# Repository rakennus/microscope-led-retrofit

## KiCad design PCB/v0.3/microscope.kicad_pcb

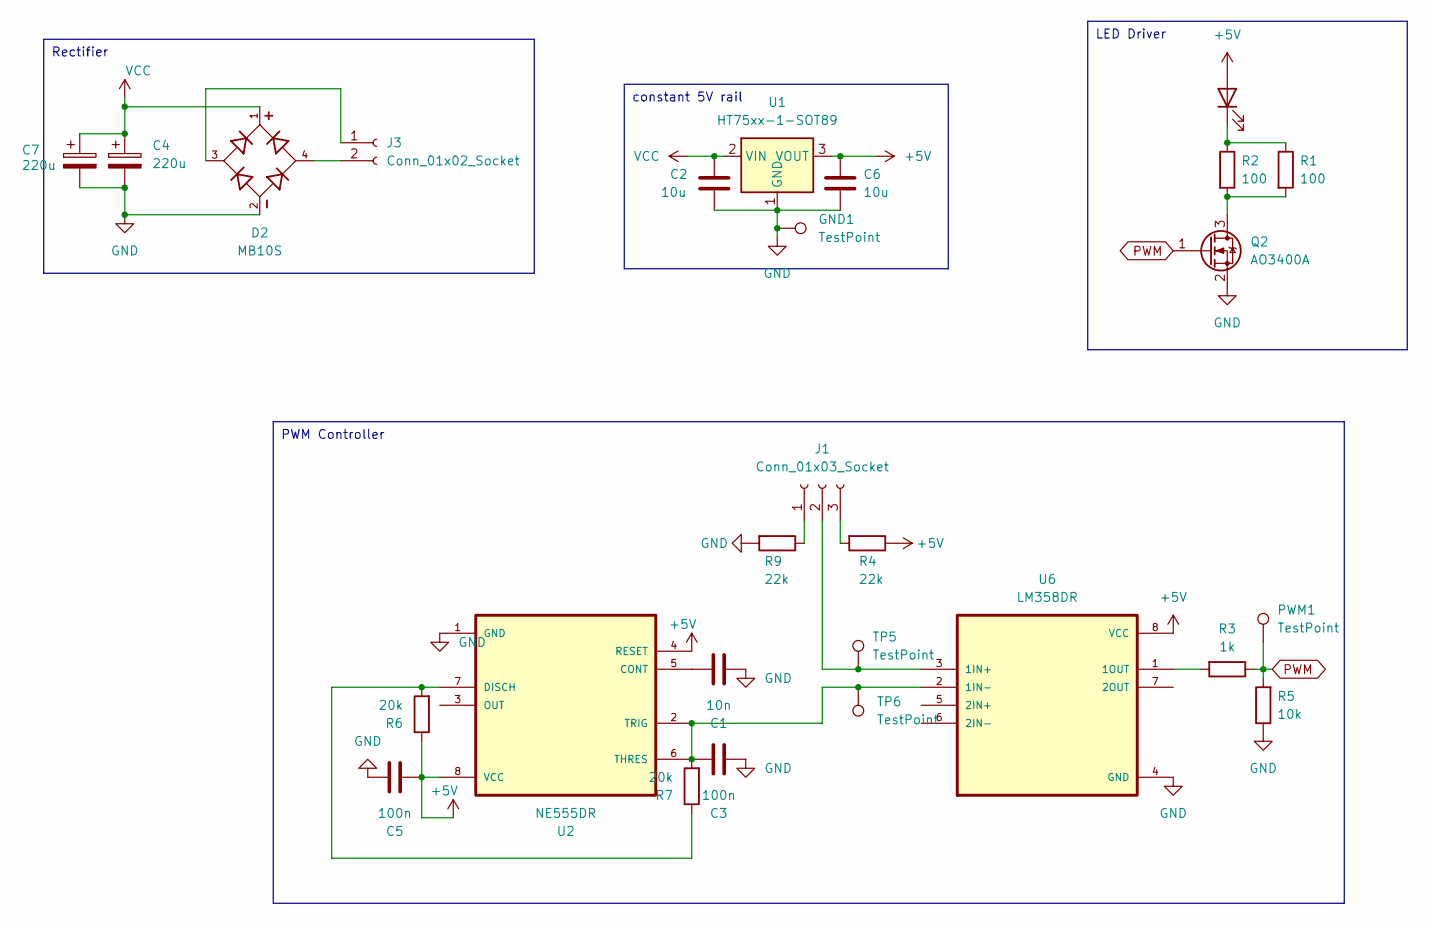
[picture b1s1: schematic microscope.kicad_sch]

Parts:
C1: 10n; C_0603_1608Metric
C2, C6: 10u; C_0603_1608Metric
C3, C5: 100n; C_0603_1608Metric
C4, C7: 220u; CP_Elec_8x6.5; LCSC C178534
D2: MB10S; SOIC245P670X290-4N; LCSC C2488
D4: LED; LED_2835; LCSC C210319
GND1: TestPoint; TestPoint_Plated_Hole_D2.0mm
J1: Conn_01x03_Socket; JST_XH_S3B-A-no-support
J3: Conn_01x02_Socket; JST_XH_S2B-A-no-support
PWM1: TestPoint; TestPoint_Plated_Hole_D2.0mm
Q2: AO3400A; SOT-23
R1, R2: 100; R_0805_2012Metric; LCSC C17408
R3: 1k; R_0603_1608Metric
R4, R9: 22k; R_0603_1608Metric
R5: 10k; R_0603_1608Metric
R6, R7: 20k; R_0603_1608Metric
TP5, TP6: TestPoint; TestPoint_Plated_Hole_D2.0mm
U1: HT75xx-1-SOT89; SOT-89-3; LCSC C347189
U2: NE555DR; SOIC127P599X175-8N; DigiKey_Part_Number 296-6501-2-ND
U6: LM358DR; SOIC127P599X175-8N; LCSC C5423

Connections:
+5V: C5.1, C6.1, D4.2 (A), R4.1, R6.1, U1.3 (VOUT), U2.4 (RESET), U2.8 (VCC), U6.8 (VCC)
GND: C1.1, C2.2, C3.2, C4.2, C5.2, C6.2, C7.2, D2.2, GND1.1, Q2.2 (S), R5.1, R9.2, U1.1 (GND), U2.1 (GND), U6.4 (GND)
unnamed: D4.1 (K), R1.1, R2.1
unnamed: J1.1, R9.1
unnamed: J1.2, TP5.1, U6.3 (1IN+)
unnamed: J1.3, R4.2
unnamed: D2.3, J3.1
unnamed: D2.4, J3.2
unnamed: Q2.3 (D), R1.2, R2.2
unnamed: C1.2, U2.5 (CONT)
unnamed: R6.2, R7.1, U2.7 (DISCH)
unnamed: C3.1, R7.2, TP6.1, U2.2 (TRIG), U2.6 (THRES), U6.2 (1IN-)
unnamed: R3.2, U6.1 (1OUT)
PWM: PWM1.1, Q2.1 (G), R3.1, R5.2
VCC: C2.1, C4.1, C7.1, D2.1, U1.2 (VIN)

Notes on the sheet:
constant 5V rail
PWM Controller
Rectifier
LED Driver

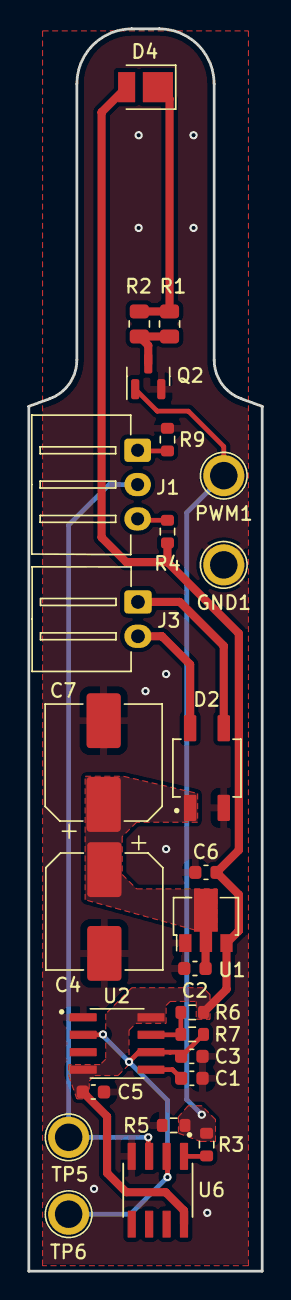
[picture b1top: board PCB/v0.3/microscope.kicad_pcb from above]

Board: 2 copper layers, 17.0 x 90.5 mm, 27 parts (0 on the bottom side), 15 nets.

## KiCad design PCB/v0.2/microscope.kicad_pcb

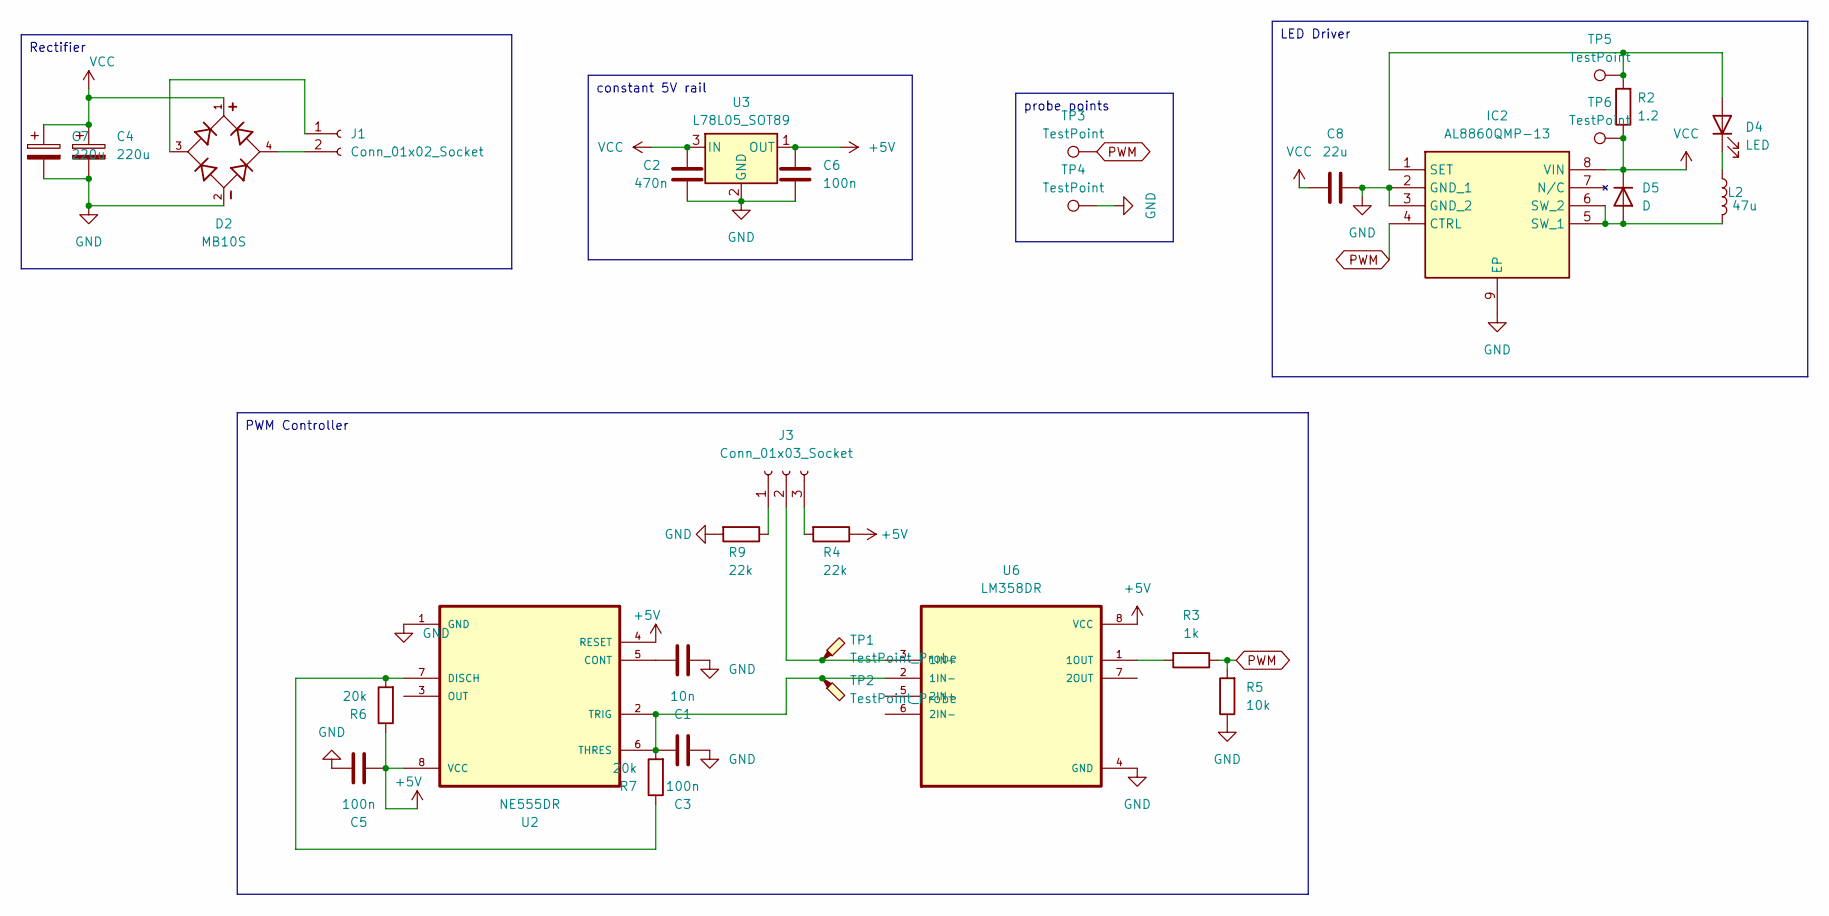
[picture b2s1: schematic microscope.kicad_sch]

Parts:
C1: 10n; C_0603_1608Metric
C2: 470n; C_0603_1608Metric
C3, C5, C6: 100n; C_0603_1608Metric
C4, C7: 220u; CP_Elec_8x6.5
C8: 22u; C_0805_2012Metric
D2: MB10S; SOIC245P670X290-4N; LCSC C2488
D4: LED; LED_PLCC_2835
D5: D; D_SOD-323; LCSC C191023
IC2: AL8860QMP-13; SOP65P490X110-9N; Manufacturer_Part_Number AL8860QMP-13; LCSC C2678649
J1: Conn_01x02_Socket; JST_XH_B2B-XH-A_1x02_P2.50mm_Vertical
J3: Conn_01x03_Socket; JST_XH_B3B-XH-A_1x03_P2.50mm_Vertical
L2: 47u; L_1210_3225Metric; LCSC C361668
R2: 1.2; R_0603_1608Metric
R3: 1k; R_0603_1608Metric
R4, R9: 22k; R_0603_1608Metric
R5: 10k; R_0603_1608Metric
R6, R7: 20k; R_0603_1608Metric
TP1, TP2: TestPoint_Probe; TestPoint_THTPad_1.0x1.0mm_Drill0.5mm
TP3, TP4, TP5, TP6: TestPoint; TestPoint_THTPad_3.0x3.0mm_Drill1.5mm
U2: NE555DR; SOIC127P599X175-8N; DigiKey_Part_Number 296-6501-2-ND
U3: L78L05_SOT89; SOT-89-3
U6: LM358DR; SOIC127P599X175-8N; LCSC C5423

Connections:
+5V: C5.1, C6.1, R4.1, R6.1, U2.4 (RESET), U2.8 (VCC), U3.1 (OUT), U6.8 (VCC)
GND: C1.1, C2.2, C3.2, C4.2, C5.2, C6.2, C7.2, C8.2, D2.2, IC2.2 (GND_1), IC2.3 (GND_2), IC2.9 (EP), R5.1, R9.2, TP4.1, U2.1 (GND), U3.2 (GND), U6.4 (GND)
unnamed: D4.2 (A), IC2.1 (SET), R2.2, TP5.1
unnamed: D4.1 (K), L2.1
unnamed: D5.2 (A), IC2.5 (SW_1), IC2.6 (SW_2), L2.2
unnamed: D2.3, J1.1
unnamed: D2.4, J1.2
unnamed: J3.1, R9.1
unnamed: J3.2, TP1.1, U6.3 (1IN+)
unnamed: J3.3, R4.2
unnamed: C1.2, U2.5 (CONT)
unnamed: R6.2, R7.1, U2.7 (DISCH)
unnamed: C3.1, R7.2, TP2.1, U2.2 (TRIG), U2.6 (THRES), U6.2 (1IN-)
unnamed: R3.2, U6.1 (1OUT)
PWM: IC2.4 (CTRL), R3.1, R5.2, TP3.1
VCC: C2.1, C4.1, C7.1, C8.1, D2.1, D5.1 (K), IC2.8 (VIN), R2.1, TP6.1, U3.3 (IN)

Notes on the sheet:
constant 5V rail
PWM Controller
Rectifier
LED Driver
probe points

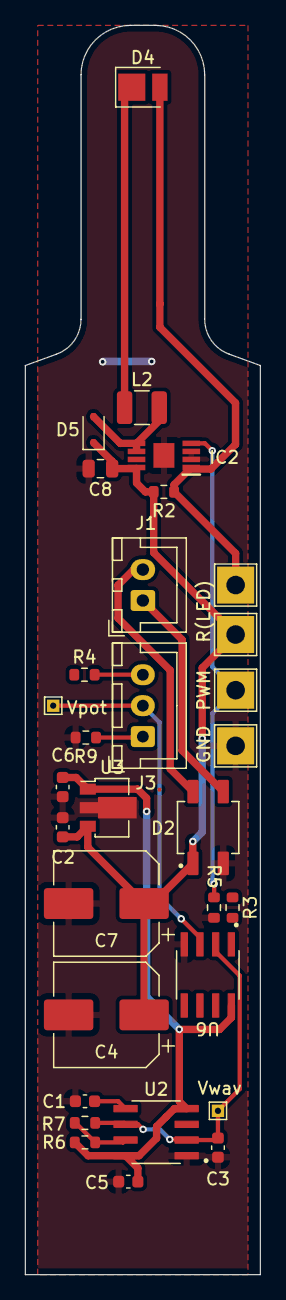
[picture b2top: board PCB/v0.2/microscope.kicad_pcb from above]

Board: 2 copper layers, 19.0 x 101.0 mm, 31 parts (0 on the bottom side), 16 nets.

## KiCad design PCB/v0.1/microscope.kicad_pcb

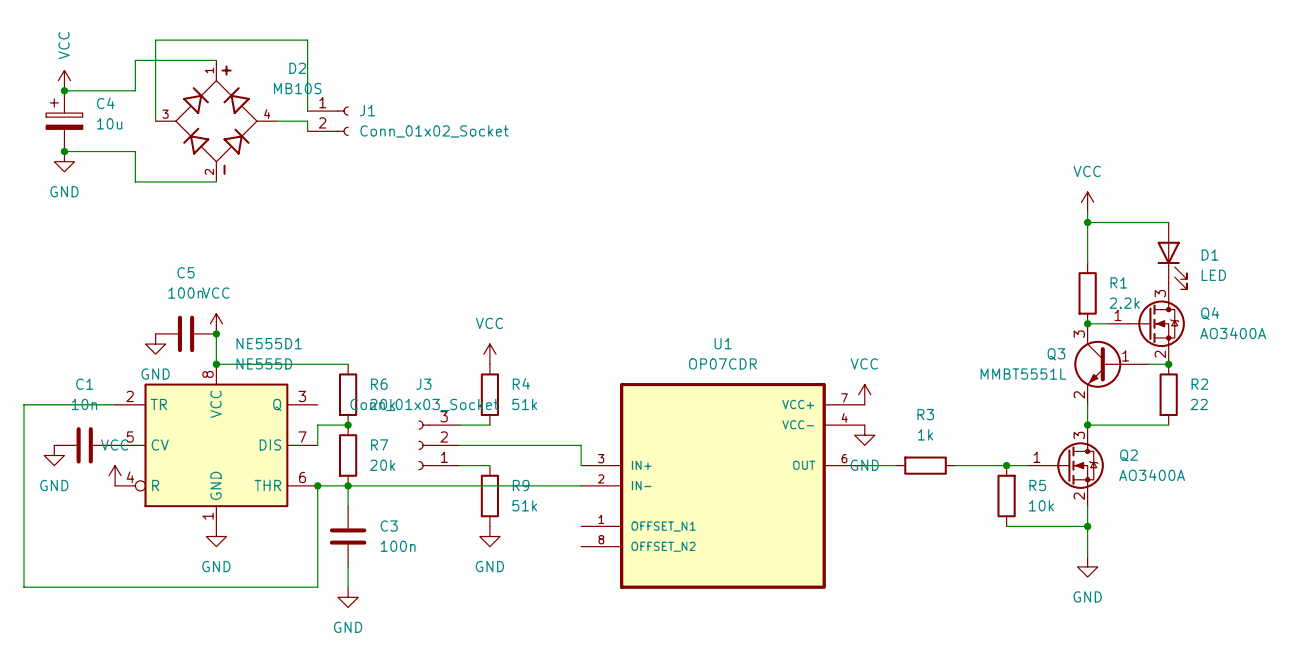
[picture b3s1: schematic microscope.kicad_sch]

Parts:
C1: 10n; C_0603_1608Metric
C3, C5: 100n; C_0603_1608Metric
C4: 10u; C_0805_2012Metric
D1: LED; LED_PLCC_2835
D2: MB10S; SOIC245P670X290-4N
J1: Conn_01x02_Socket; JST_XH_B2B-XH-A_1x02_P2.50mm_Vertical
J3: Conn_01x03_Socket; JST_XH_B3B-XH-A_1x03_P2.50mm_Vertical
NE555D1: NE555D; SOIC-8_3.9x4.9mm_P1.27mm
Q2, Q4: AO3400A; SOT-23
Q3: MMBT5551L; SOT-23
R1: 2.2k; R_0603_1608Metric
R2: 22; R_1206_3216Metric
R3: 1k; R_0603_1608Metric
R4, R9: 51k; R_0603_1608Metric
R5: 10k; R_0603_1608Metric
R6, R7: 20k; R_0603_1608Metric
U1: OP07CDR; SOIC127P599X175-8N

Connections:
GND: C1.1, C3.1, C4.2, C5.2, D2.2, NE555D1.1 (GND), Q2.2 (S), R5.1, R9.2, U1.4 (VCC-)
unnamed: D1.1 (K), Q4.3 (D)
unnamed: D2.3, J1.1
unnamed: D2.4, J1.2
unnamed: J3.1, R9.1
unnamed: J3.2, U1.3 (IN+)
unnamed: J3.3, R4.2
unnamed: C1.2, NE555D1.5 (CV)
unnamed: NE555D1.7 (DIS), R6.2, R7.1
unnamed: C3.2, NE555D1.2 (TR), NE555D1.6 (THR), R7.2, U1.2 (IN-)
unnamed: Q2.3 (D), Q3.2 (E), R2.2
unnamed: Q2.1 (G), R3.1, R5.2
unnamed: Q3.1 (B), Q4.2 (S), R2.1
unnamed: Q3.3 (C), Q4.1 (G), R1.2
unnamed: R3.2, U1.6 (OUT)
VCC: C4.1, C5.1, D1.2 (A), D2.1, NE555D1.4 (R), NE555D1.8 (VCC), R1.1, R4.1, R6.1, U1.7 (VCC+)

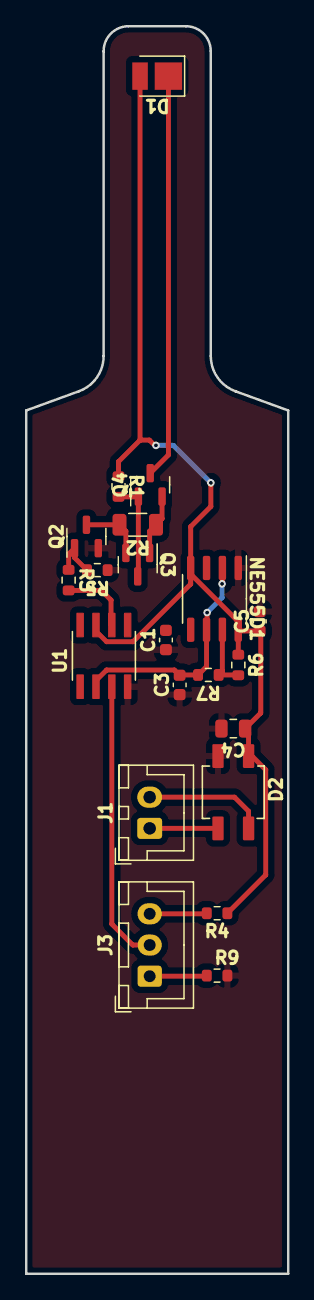
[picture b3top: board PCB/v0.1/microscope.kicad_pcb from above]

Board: 2 copper layers, 21.0 x 100.0 mm, 21 parts (0 on the bottom side), 16 nets.

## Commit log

2024-02-28 changes lol
2024-03-07 v0.2 pcb finished
2024-04-17 change
2024-06-11 tweaking
